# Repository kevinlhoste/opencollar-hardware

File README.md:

# opencollar-hardware
Hardware files of the dog collar project

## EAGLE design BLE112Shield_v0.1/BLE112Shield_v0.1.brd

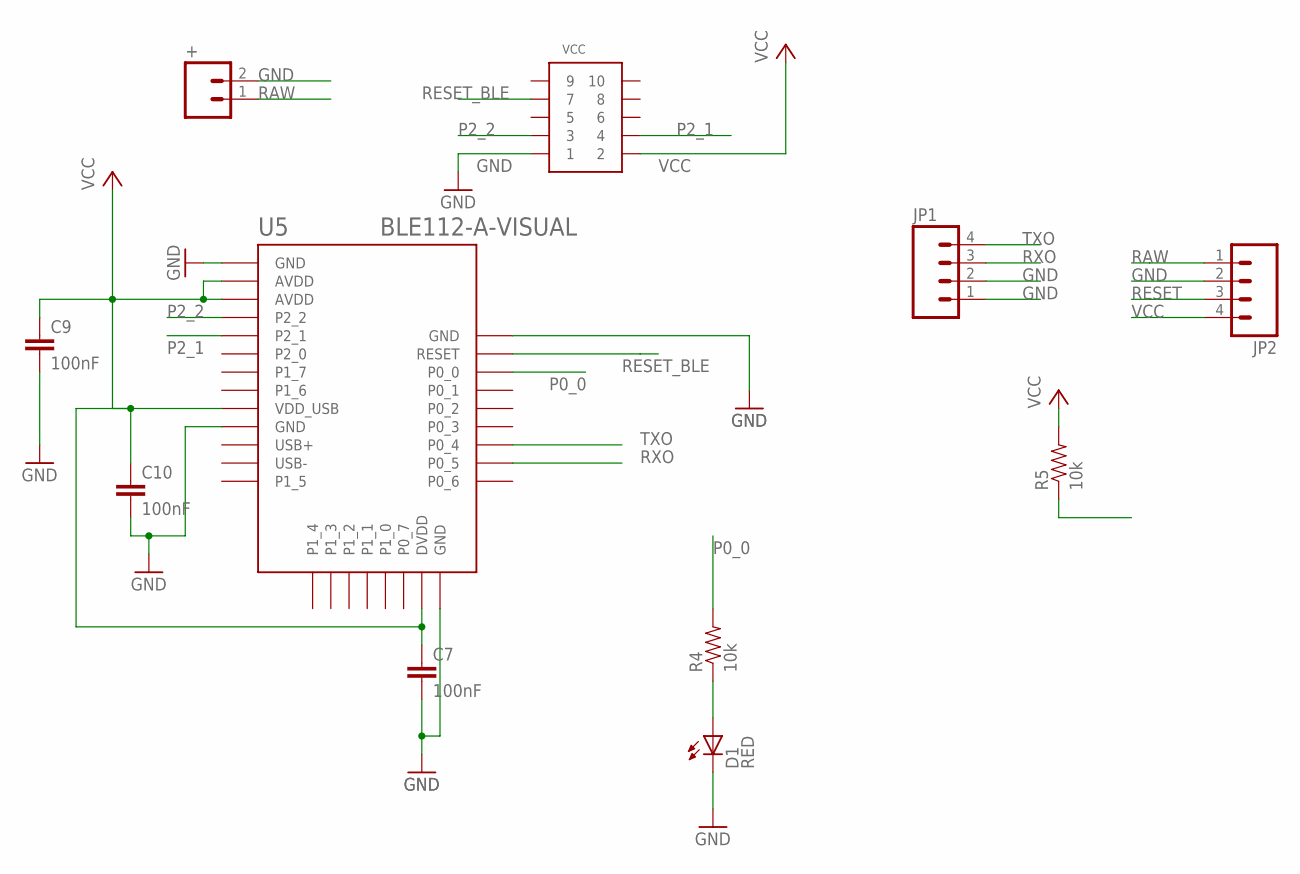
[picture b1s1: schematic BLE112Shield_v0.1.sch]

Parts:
+: M021X02_NO_SILK; 1X02_NO_SILK
C7, C9, C10: 100nF; 0402-CAP
D1: RED; LED-0603
JP1, JP2: M04PTH; 1X04
R4, R5: 10k; 0402-RES
U5: BLE112-A-VISUAL; BLE112-A
VCC: CONN_5-2-FTSH-V; FTSH-105-DV

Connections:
GND: +.2, C7.2, C9.2, C10.2, D1.C, JP1.1, JP1.2, JP2.2, U5.GND1 (GND), U5.GND2 (GND), U5.GND3 (GND), U5.GND4 (GND), VCC.1
unnamed: D1.A, R4.1
P0_0: R4.2, U5.P0_0
P2_1: U5.P2_1, VCC.4
P2_2: U5.P2_2, VCC.3
RAW: +.1, JP2.1
RESET: JP2.3
RESET_BLE: R5.1, U5.RESET, VCC.7
RXO: JP1.3, U5.P0_5
TXO: JP1.4, U5.P0_4
VCC: C7.1, C9.1, C10.1, JP2.4, R5.2, U5.AVDD1 (AVDD), U5.AVDD2 (AVDD), U5.DVDD, U5.VDD_USB, VCC.2

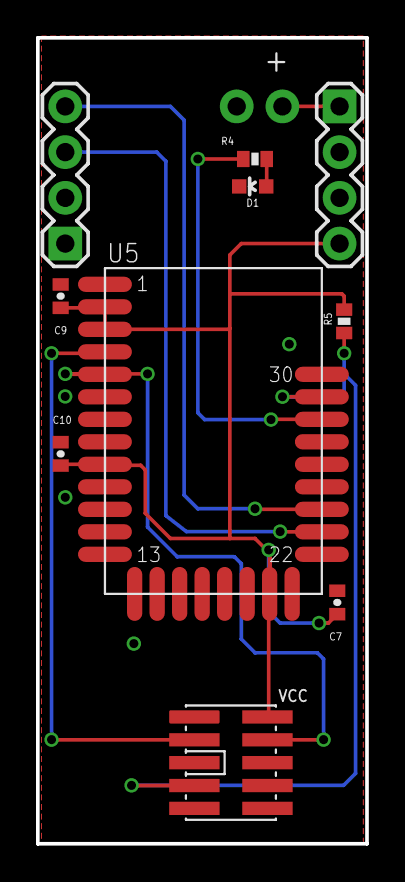
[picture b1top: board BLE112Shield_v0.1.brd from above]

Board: 4 copper layers, 18.3 x 44.8 mm, 11 parts (0 on the bottom side), 10 nets.

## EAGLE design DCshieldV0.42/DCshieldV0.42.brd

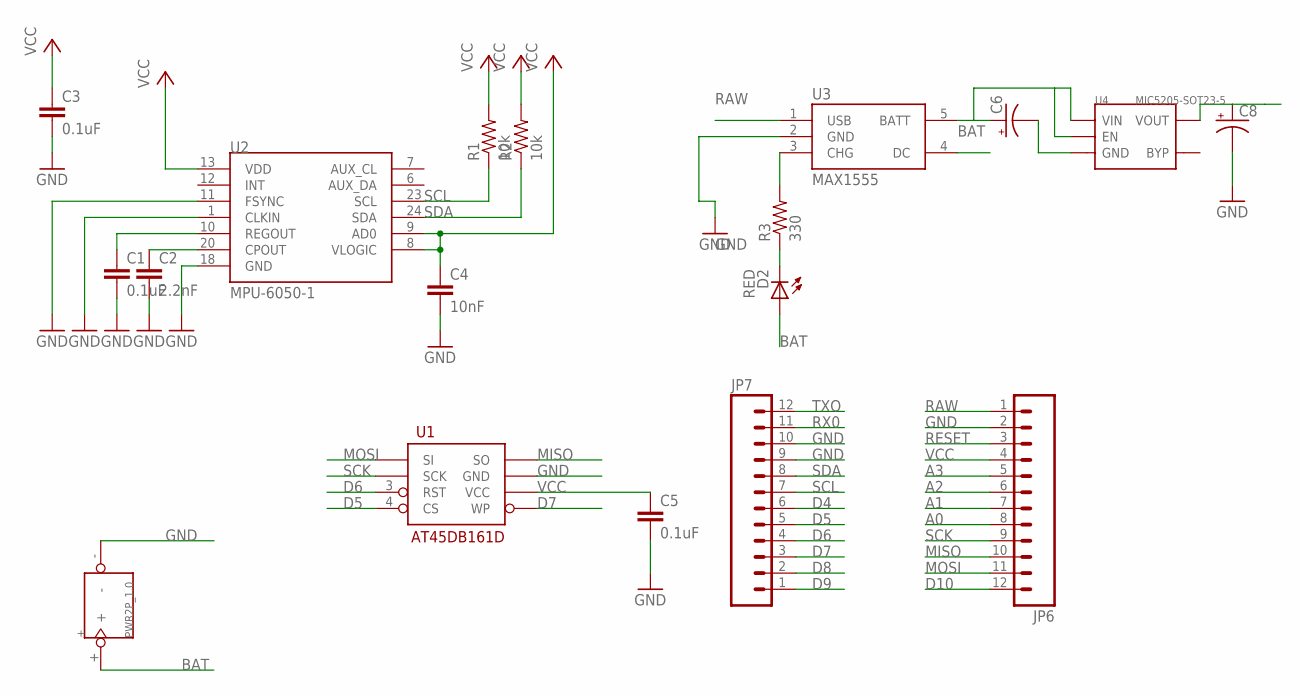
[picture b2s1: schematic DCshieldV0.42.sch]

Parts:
+: PWR2P_1.0
C1, C3, C5: 0.1uF; 0402-CAP
C2: 2.2nF; 0402-CAP
C4: 10nF; 0402-CAP
C6, C8: CAP_POL1206; EIA3216
D2: RED; LED-0603
JP6, JP7: M12PTH; 1X12
R1, R2: 10k; 0402-RES
R3: 330; 0402-RES
U1: AT45DB161D; SO08-EIAJ
U2: MPU-6050-1; QFN-24-4MM2
U3: MAX1555; SOT23-5
U4: MIC5205-SOT23-5; SOT23-5

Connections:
A0: JP6.8
A1: JP6.7
A2: JP6.6
A3: JP6.5
BAT: +.+, C6.A (+), D2.A, U3.5 (BATT), U4.1 (VIN), U4.3 (EN)
D4: JP7.6
D5: JP7.5, U1.4 (CS)
D6: JP7.4, U1.3 (RST)
D7: JP7.3, U1.5 (WP)
D8: JP7.2
D9: JP7.1
D10: JP6.12
GND: +.-, C1.2, C2.2, C3.2, C4.2, C5.2, C6.C (-), C8.C (-), JP6.2, JP7.9, JP7.10, U1.7 (GND), U2.1 (CLKIN), U2.11 (FSYNC), U2.18 (GND), U3.2 (GND), U4.2 (GND)
MISO: JP6.10, U1.8 (SO)
MOSI: JP6.11, U1.1 (SI)
unnamed: C1.1, U2.10 (REGOUT)
unnamed: C2.1, U2.20 (CPOUT)
unnamed: R3.2, U3.3 (CHG)
unnamed: D2.C, R3.1
RAW: JP6.1, U3.1 (USB), U3.4 (DC)
RESET: JP6.3
RX0: JP7.11
SCK: JP6.9, U1.2 (SCK)
SCL: JP7.7, R1.1, U2.23 (SCL)
SDA: JP7.8, R2.1, U2.24 (SDA)
TXO: JP7.12
VCC: C3.1, C4.1, C5.1, C8.A (+), JP6.4, R1.2, R2.2, U1.6 (VCC), U2.8 (VLOGIC), U2.9 (AD0), U2.13 (VDD), U4.5 (VOUT)

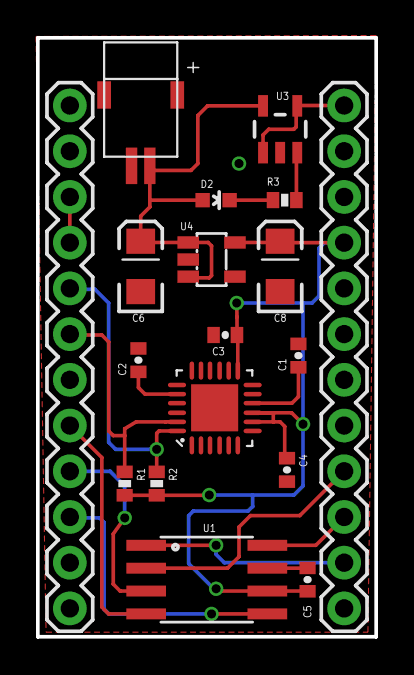
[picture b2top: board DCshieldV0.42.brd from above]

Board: 2 copper layers, 18.8 x 33.3 mm, 18 parts (0 on the bottom side), 16 nets.

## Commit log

2016-07-10 Added DCshieldV0.42 files
2016-07-10 Added BLE112 Shield for Sparkfun pro micro

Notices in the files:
parts and their libraries:
SparkFun-Connectors: Licensing: CC v3.0 Share-Alike You are welcome to use this library for commercial purposes.
